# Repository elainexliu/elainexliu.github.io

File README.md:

# elainexliu.github.io

working on moving my personal website to github

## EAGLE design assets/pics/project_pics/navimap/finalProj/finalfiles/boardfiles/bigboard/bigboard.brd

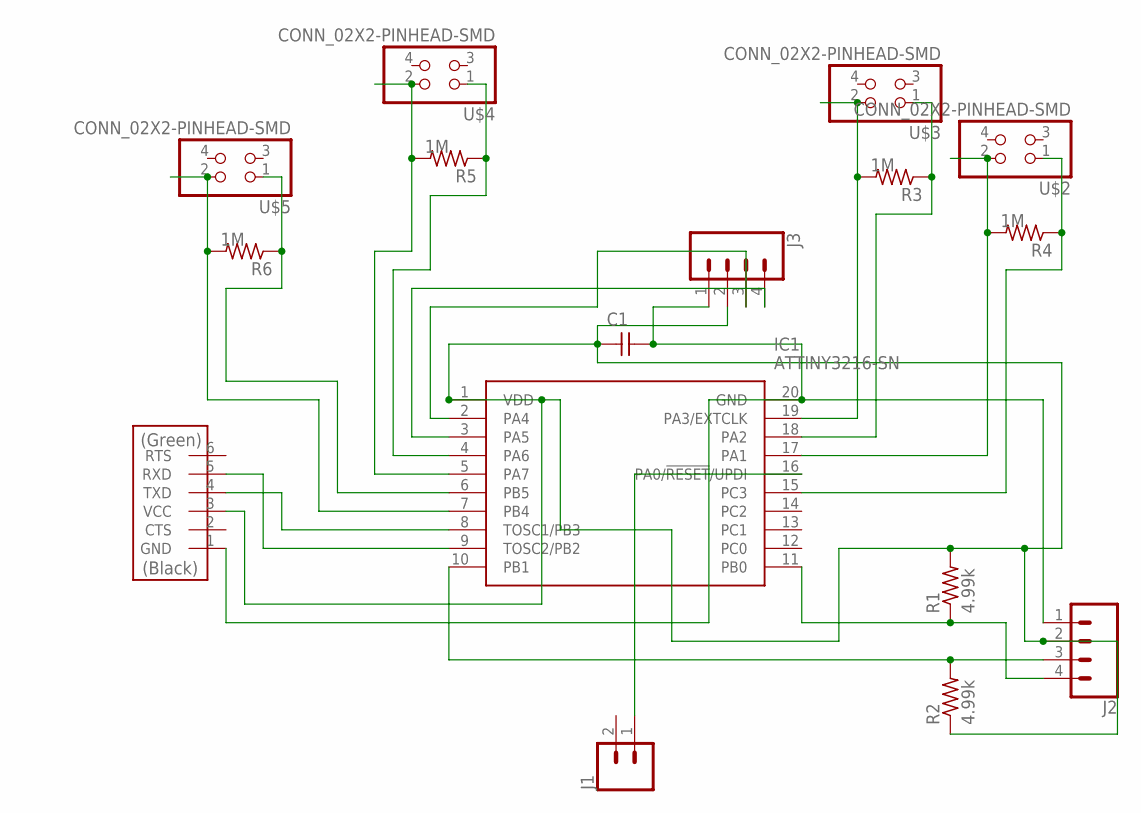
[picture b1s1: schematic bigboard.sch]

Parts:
C1: CAP_UNPOLARIZEDFAB; C1206FAB
IC1: ATTINY3216-SN; SOIC127P1030X265-20N
J1: CONN_02LOCK_LONGPADS; 1X02_LOCK_LONGPADS
J2, J3: CONN_04SMD_LONG; 1X04_SMD_LONG
R1, R2: 4.99k; R1206FAB
R3, R4, R5, R6: R1206FAB
U$1: CONN_06_FTDI-SMD-HEADER; 1X06SMD
U$2, U$3, U$4, U$5: CONN_02X2-PINHEAD-SMD; 2X02SMD

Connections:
unnamed: IC1.17 (PA1), R4.2, U$2.2
unnamed: IC1.15 (PC3), R4.1, U$2.1
unnamed: IC1.19 (PA3/EXTCLK), R3.2, U$3.2
unnamed: IC1.18 (PA2), R3.1, U$3.1
unnamed: IC1.5 (PA7), R5.2, U$4.2
unnamed: IC1.4 (PA6), R5.1, U$4.1
unnamed: IC1.7 (PB4), R6.2, U$5.2
unnamed: IC1.6 (PB5), R6.1, U$5.1
unnamed: IC1.9 (TOSC2/PB2), U$1.5 (RXD)
unnamed: C1.2, IC1.20 (GND), J2.1, J3.1, U$1.1 (GND)
unnamed: IC1.16 (PA0/!RESET!/UPDI), J1.1
unnamed: IC1.2 (PA4), J3.3
unnamed: IC1.3 (PA5), J3.4
unnamed: IC1.10 (PB1), J2.3, R2.2
unnamed: C1.1, IC1.1 (VDD), J2.2, J3.2, R1.2, R2.1, U$1.3 (VCC)
unnamed: IC1.11 (PB0), J2.4, R1.1
unnamed: IC1.8 (TOSC1/PB3), U$1.4 (TXD)

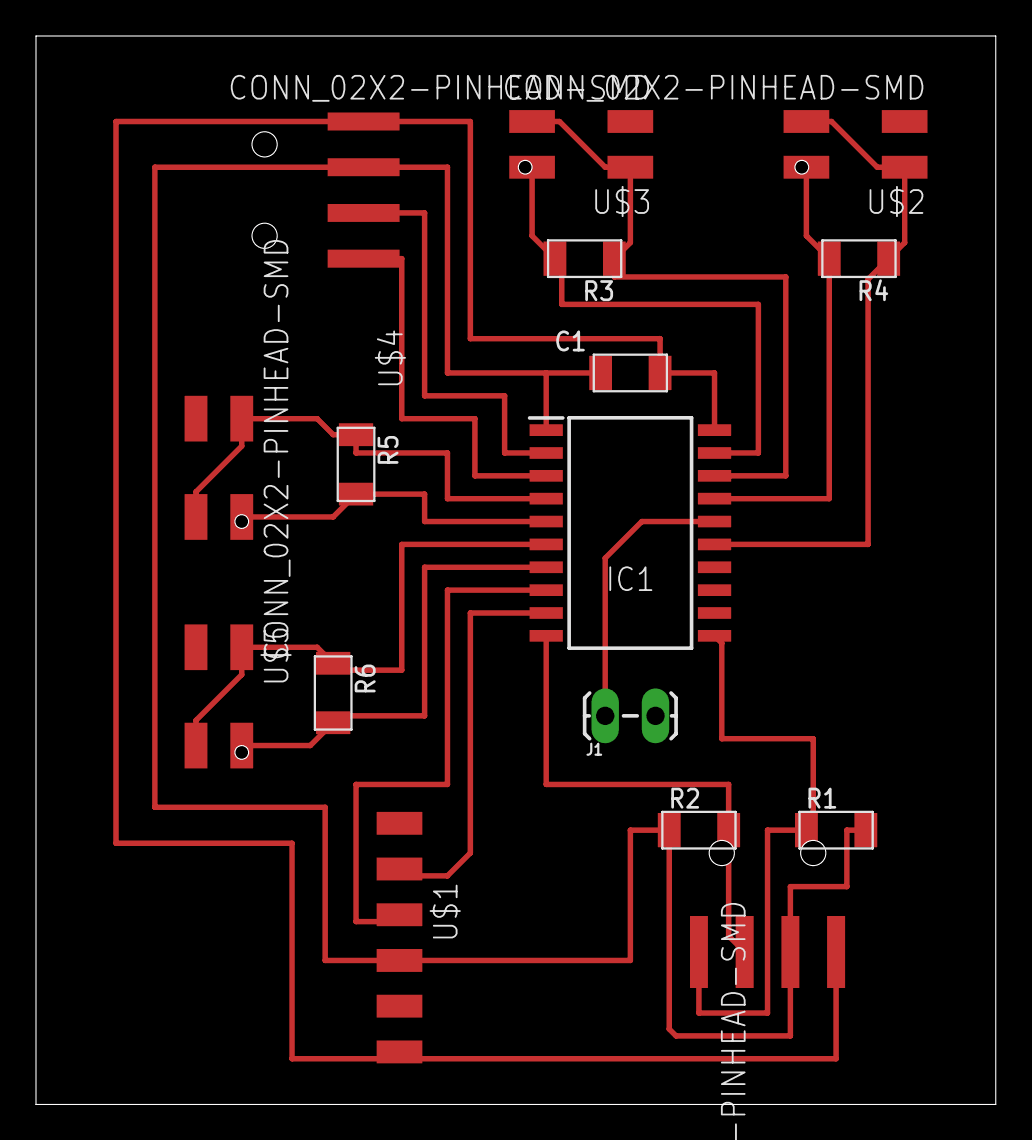
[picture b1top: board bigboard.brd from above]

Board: 2 copper layers, 53.3 x 59.4 mm, 16 parts (0 on the bottom side), 17 nets.

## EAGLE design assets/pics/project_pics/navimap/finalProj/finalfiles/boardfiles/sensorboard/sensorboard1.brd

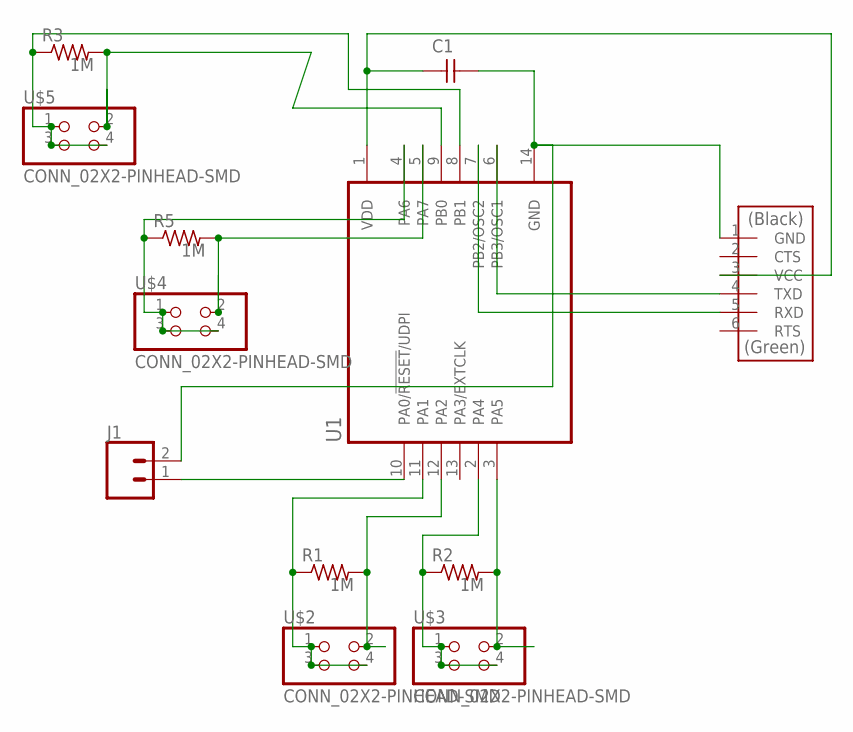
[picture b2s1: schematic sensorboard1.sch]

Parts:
C1: CAP_UNPOLARIZEDFAB; C1206FAB
J1: CONN_02LOCK_LONGPADS; 1X02_LOCK_LONGPADS
R1, R2, R3, R5: R1206FAB
U1: ATTINY1614-SSNR; SOIC127P600X175-14N
U$1: CONN_06_FTDI-SMD-HEADER; 1X06SMD
U$2, U$3, U$4, U$5: CONN_02X2-PINHEAD-SMD; 2X02SMD

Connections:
unnamed: R1.2, U1.12 (PA2), U$2.2
unnamed: R1.1, U1.11 (PA1), U$2.1, U$2.3, U$2.4
unnamed: R2.2, U1.3 (PA5), U$3.2
unnamed: R2.1, U1.2 (PA4), U$3.1, U$3.3, U$3.4
unnamed: R5.2, U1.5 (PA7), U$4.2
unnamed: R5.1, U1.4 (PA6), U$4.1, U$4.3, U$4.4
unnamed: C1.2, J1.2, U1.14 (GND), U$1.1 (GND)
unnamed: R3.2, U1.9 (PB0), U$5.2
unnamed: R3.1, U1.8 (PB1), U$5.1, U$5.3, U$5.4
unnamed: J1.1, U1.10 (PA0/!RESET!/UDPI)
unnamed: C1.1, U1.1 (VDD), U$1.3 (VCC)
unnamed: U1.6 (PB3/OSC1), U$1.4 (TXD)
unnamed: U1.7 (PB2/OSC2), U$1.5 (RXD)

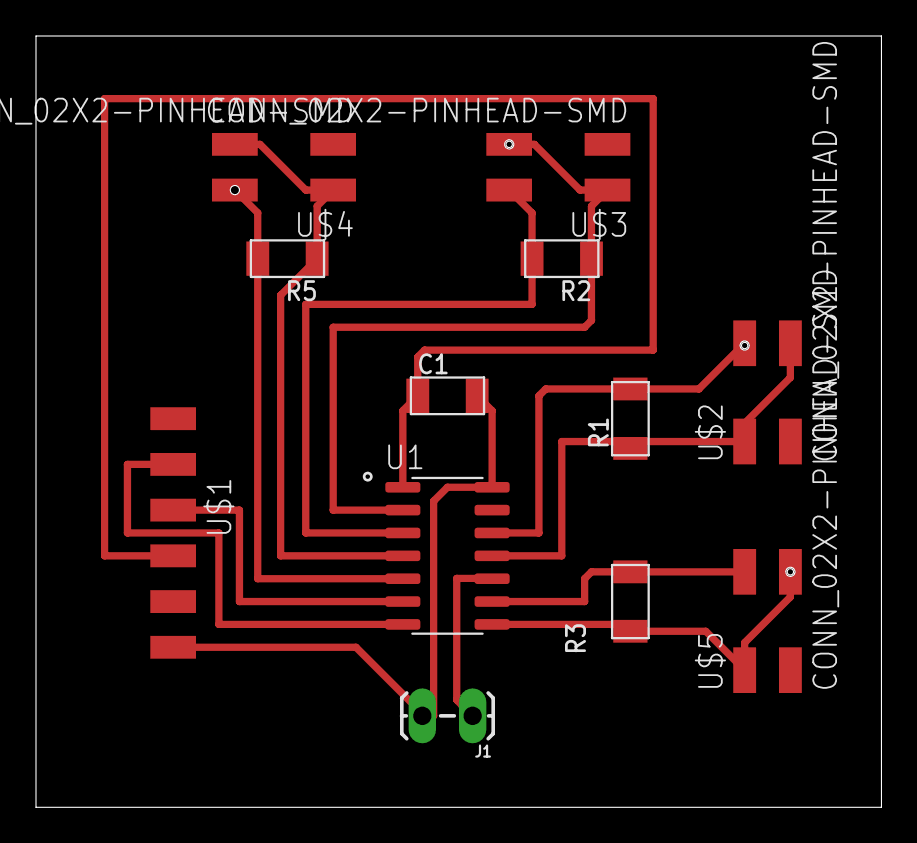
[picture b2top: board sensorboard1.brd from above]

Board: 2 copper layers, 47.0 x 42.9 mm, 12 parts (0 on the bottom side), 13 nets.

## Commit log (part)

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2023-07-07 changing writing display
2023-07-07 fixing some bugs
2023-07-07 trying
2023-07-10 fix: trying to fix things
2023-07-10 fix: starting to work...
2023-07-10 fix: maybe..
2023-07-10 fix: trying
2023-07-10 fix: probably not
2023-07-10 fix: not rly
2023-07-11 fix: rearranging
2023-07-11 fix: testing
2023-07-11 fix: maybe??
2023-07-11 fix: perhaps
2023-07-11 fix: please bro
2023-07-11 fix: url bro
2023-07-11 fix: fingers crossed
2023-07-11 fix: it's starting to work???
2023-07-11 fix: almost there...
2023-07-11 fix: PLEASE
2023-07-11 fix: getting there, testing out tags
2023-07-11 fix: tags again
2023-07-11 feat: projects
2023-07-11 fix: project page again
2023-07-11 fix: writing not looping through tags
2023-07-11 fix: capitalizing an h
2023-07-11 fix: projects
2023-07-11 fix: reconfiguring to html
2023-07-11 fix: ok jk that didn't work
2023-07-11 fix: config to match
2023-07-11 fix: please work
2023-07-11 fix: attempting to make things look pretty
2023-07-11 fix: trying pictures
2023-07-11 fix: testing the image link
2023-07-11 fix: testing lantern pic
2023-07-11 fix: testing images with the post layout instead
2023-07-11 fix: testing out positioning of pic
2023-07-11 fix: testing actual image on site
2023-07-11 fix: testing this out
2023-07-11 fix: more pic testing
2023-07-11 fix: seeing what the post title is
2023-07-11 fix: testing project types
2023-07-11 fix: got rid of the script for the string
2023-07-11 fix: bottom nav
2023-07-11 fix: nvm on the bottom navbar
2023-07-12 fix: changed the default color
2023-07-12 fix: updated index
2023-07-14 fix: updated projects page
2023-07-14 fix: labyrinth box
2023-07-14 fix: added the foldable phone stand
2023-07-14 fix: added the projects
2023-07-14 fix: home page and stuff
2023-07-14 fix: index
2023-07-14 fix: font sizing
2023-07-14 fix: index projects
2023-07-14 fix: testing colors
2023-07-14 fix: getting rid of navlinks
2023-07-15 fix: trying to get rid of highlights
2023-07-15 fix: ok jk it didn't work
2023-07-15 fix: trying to get rid of the posts highlights
2023-07-15 fix: footer
2023-07-15 fix: maybe this is it
2023-07-15 fix: footer again
2023-07-15 fix: probably not the fix
2023-07-15 fix: adding a pic to deng long
2023-07-15 fix: refixing the footer
2023-07-16 fix: changing back bc it didn't work
2023-07-16 fix: testing width
2023-07-16 fix: weird top margin
2023-07-17 fix: margins
2023-07-17 fix: just the margin
2023-07-17 fix: margin 0 auto
2023-07-17 fix: testing wrapping
2023-07-17 fix: width
2023-07-17 fix: home page wording
2023-07-17 fix: writing posts
2023-07-17 fix: labyrinth post documentation included
2023-07-17 fix: foldable documentation
2023-07-17 fix: added foldable pics
2023-07-17 fix: maybe an embed?
2023-07-18 fix: solar text
2023-07-18 fix: chatgpt pls come through
2023-07-18 fix: seeing what happens
2023-07-18 fix: pls bro
2023-07-18 fix: sM!
2023-07-19 fix: index and projects
2023-07-19 fix: project reformatting
2023-07-19 fix: portfolios font size
2023-07-19 fix: project names on index
2023-07-19 fix: normal font size
2023-07-28 fix: solar pics
2023-07-28 fix: pictures added
2023-07-28 fix: stance-vid
2023-07-28 fix: description for the image videos
2023-08-02 fix: retitled blog post
2023-09-23 chore: updating res
2023-09-26 fix: width on phone
2023-09-26 fix: width for phone
2023-09-26 fix: pls
2023-09-26 fix: trying to fix overflow on mobile
2023-09-26 fix: postpone a blogpost
2023-09-26 fix: text wrap pls
2023-09-26 fix: getting warmer
2023-09-26 fix: including the pic
2023-09-26 fix: 85% instead, pic worked
2023-09-26 fix: 95%
2023-09-26 fix: 100% width
2023-09-26 fix: new res
2023-09-26 fix: recollection!
2023-09-26 fix: res
2023-10-02 feat: agora!
2023-10-02 feat: agora on home page
2023-10-02 fix: agora
2023-10-02 fix: home page
2024-08-18 moved pics
2024-08-18 trying the posts section again
2024-08-18 test
2024-08-18 hiding some posts
2024-08-18 testing width
2024-08-18 testing max-width
2024-08-18 max width 50
2024-08-18 font size
2024-08-18 Create CNAME
2024-08-18 cname
2024-08-18 max-width
2024-08-18 lowercase
2024-08-18 get rid of sharelinks
2024-08-18 65 width
2024-08-18 smaller font size
2024-08-18 adjusted the top section
2024-10-13 fix(home): some text
2024-10-13 fix(pfp and home): text and bottom margin
2024-10-13 fix(pfp): more padding
2024-10-13 fix(pfp): again
2024-10-13 fix(pfp): spacing
2024-10-15 feat: amber!
2024-10-16 fix: amber image alert
2024-10-16 futfeat(copal)
2024-10-18 fix(amber): new amberdata and edit sound pics
2024-10-21 test adding footer socials
2024-10-21 more on one piece
2024-10-21 jk on the footer
2024-10-26 temp feat: for dynasty
2024-10-26 putting on home page
2024-10-26 small change
2024-10-26 fix: m-port link
2024-12-31 fixes to home page
2024-12-31 project updates
2024-12-31 writing updates
2024-12-31 agora update vid test
2024-12-31 agora vid test
2024-12-31 small
2024-12-31 embed
2024-12-31 copal
2024-12-31 cusd
2024-12-31 updates project
2024-12-31 some new writing
2025-01-18 edit: new essay
2025-01-18 edits
2025-01-18 edit: miro
2025-01-18 edits: font and home
2025-01-18 edit: home
2025-01-18 fix: home
2025-01-19 fix: font size
2025-01-19 edit: font
2025-01-19 edit text
2025-01-19 edit old essay
2025-01-19 edit: econ
2025-01-19 edit: small margin
2025-01-19 edit: page css
2025-01-19 edit: header
2025-01-19 edit: h1 margin
2025-01-19 edit: jk margin now
2025-01-19 edit: writing blip
2025-01-19 edit: no more gross font
2025-01-19 edit: jk on the heading
2025-01-19 edit: hashtag quirky
2025-01-19 edit: consistency
2025-01-19 edit: edits
2025-01-19 edit: trying
2025-01-19 edit: pic edits
2025-01-19 edit: title
2025-01-19 edit: transcendental
2025-01-19 edit: adjustment
2025-01-19 edit: refix
2025-05-27 rephrase
2025-05-27 out loud
2025-05-27 fixx
2025-05-27 emg push
2025-06-08 miro updates
2025-06-08 miro pdlc voltage issue
2025-08-11 v2 updates
2025-08-11 top bar
2025-08-11 udpate header
2025-08-11 projects page css
2025-08-11 edit: bringing back the header
2025-08-11 home updates
2025-08-11 individual project page edits
2025-08-12 entry page style update
2025-08-12 update blue-grey
2025-08-12 header update
2025-08-12 rip minimal
2025-08-12 header and linking issues
2025-08-12 header again and linkage
2025-08-12 more header updates
2025-08-12 more header edits
2025-08-12 image updates
2025-08-12 updated home section
2025-08-12 column attempt 2
2025-08-12 font change
2025-08-16 adding pose
2025-08-16 pmf pause
2025-08-16 added EMG pic
2025-08-16 added alterego
2025-08-16 added diffamp layout
2025-08-16 writing page
2025-08-16 play
2025-08-16 more play
2025-08-17 play title
2025-09-08 updated home page
2025-10-26 edits: updates on some of the writings
2025-10-27 publish improv
2025-10-27 edits on improv text
2025-10-27 capitalize i in improv
2025-10-27 diffamp layout
2025-10-27 changing improv date
2025-10-28 putting on the site
2025-10-28 updates on snippets of life
2025-10-28 editing page
2025-10-29 updates to improv
2025-11-03 adding improved
2025-12-21 some new thoughts
2025-12-21 brief edit
2025-12-21 anotha one
2025-12-21 bullet points
2025-12-21 new trace
2025-12-22 diffamp
2025-12-22 favicon
2025-12-22 favicon index include
2025-12-22 relink for diffamp
2025-12-22 passgate simulation pics
2025-12-22 more simulation for diffamp components
2025-12-22 some spacing things
2025-12-22 bad writing lol
2025-12-22 grammar
2025-12-22 acting and improv
2026-03-08 new home page
2026-03-08 renaming pose
2026-03-08 some project edits
2026-03-12 edit
2026-03-16 on venture
2026-03-16 trace edits
2026-03-16 vanguard
2026-03-16 trace edit
2026-03-16 wireframes
2026-03-16 render additions
2026-03-16 whiterenders
2026-03-16 changed alterego thumbnail
2026-06-04 the real education starts now
2026-06-04 updated inputs
2026-06-04 new favi

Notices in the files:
parts and their libraries:
SparkFun-Connectors: Licensing: Creative Commons ShareAlike 4.0 International - https://creativecommons.org/licenses/by-sa/4.0
